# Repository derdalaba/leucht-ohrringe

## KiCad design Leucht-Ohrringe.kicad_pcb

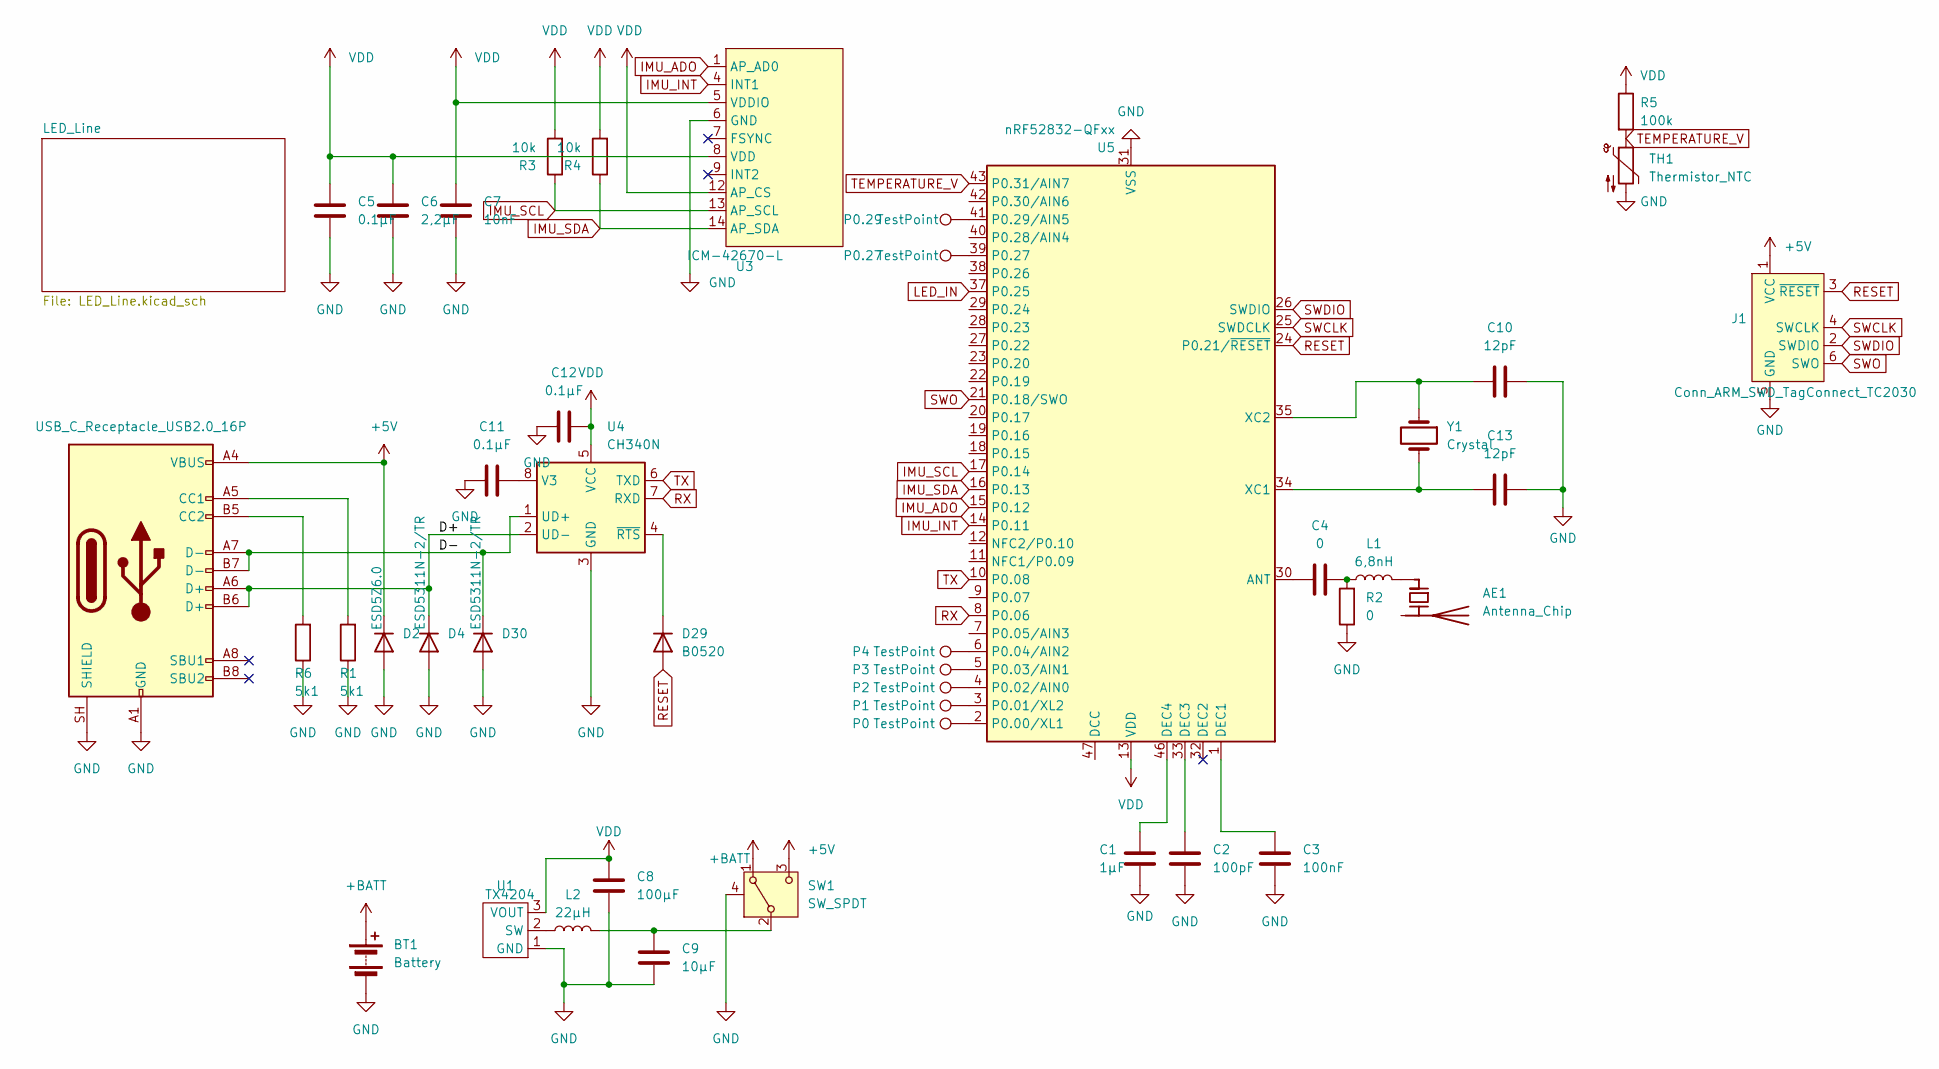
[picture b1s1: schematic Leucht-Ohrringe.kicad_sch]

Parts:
AE1: Antenna_Chip; RFANT3216120A5T; LCSC C127629
BT1: Battery; JST_SH_SM02B-SRSS-TB_1x02-1MP_P1.00mm_Horizontal
C1: 1µF; C_0402_1005Metric; LCSC C52923
C2: 100pF; C_0402_1005Metric; LCSC C1546
C3: 100nF; C_0402_1005Metric; LCSC C1525
C4: 0; C_0402_1005Metric; LCSC C17168
C5, C11, C12: 0.1µF; C_0402_1005Metric_Pad0.74x0.62mm_HandSolder; LCSC C1525
C6: 2,2µF; C_0402_1005Metric_Pad0.74x0.62mm_HandSolder; LCSC C12530
C7: 10nF; C_0402_1005Metric_Pad0.74x0.62mm_HandSolder; LCSC C15195
C8: 100µF; C_1206_3216Metric_Pad1.33x1.80mm_HandSolder; LCSC C15008
C9: 10µF; C_0603_1608Metric_Pad1.08x0.95mm_HandSolder; LCSC C19702
C10, C13: 12pF; C_0402_1005Metric; LCSC C106201
D2: ESD5Z6.0; D_SOD-523; LCSC C49437732
D4, D30: ESD5311N-2/TR; D_SOD-882; LCSC C153721
D29: B0520; D_SOD-523; LCSC C2910120
J1: Conn_ARM_SWD_TagConnect_TC2030; Tag-Connect_TC2030-IDC-NL_2x03_P1.27mm_Vertical
L1: 6,8nH; L_0402_1005Metric; LCSC C77110
L2: 22µH; FNR3015S; LCSC C167761
LCSC1: USB_C_Receptacle_USB2.0_16P; LCSC C668623
P0, P0.27, P0.29, P1, P2, P3, P4: TestPoint; TestPoint_Pad_D1.0mm
R1, R6: 5k1; R_0603_1608Metric; LCSC C2907044
R2: 0; R_0402_1005Metric; LCSC C17168
R3, R4: 10k; R_0402_1005Metric_Pad0.72x0.64mm_HandSolder; LCSC C49247682
R5: 100k; R_0402_1005Metric_Pad0.72x0.64mm_HandSolder; LCSC C25741
SW1: SW_SPDT; K3-1236S
TH1: Thermistor_NTC; R_0402_1005Metric_Pad0.72x0.64mm_HandSolder; LCSC C49247682
U1: TX4204; SOT-23-3; LCSC C5122342
U3: ICM-42670-L; Bosch_LGA-14_3x2.5mm_P0.5mm; LCSC C49073546
U4: CH340N; JEITA_SOIC-8_3.9x4.9mm_P1.27mm; LCSC C2977777
U5: nRF52832-QFxx; QFN-48-1EP_6x6mm_P0.4mm_EP4.6x4.6mm
Y1: Crystal; Crystal_SMD_2016-4Pin_2.0x1.6mm; LCSC C2682773

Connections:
+5V: D2.1 (K), J1.1 (VCC), LCSC1.A4 (VBUS), LCSC1.A9 (VBUS), LCSC1.B4 (VBUS), LCSC1.B9 (VBUS), SW1.3 (C); also elsewhere on the board
+BATT: BT1.1 (+), SW1.1 (A); also elsewhere on the board
/D+: D4.1 (K), LCSC1.A6 (D+), LCSC1.B6 (D+), U4.2 (UD-); also elsewhere on the board
/D-: D30.1 (K), LCSC1.A7 (D-), LCSC1.B7 (D-), U4.1 (UD+); also elsewhere on the board
GND: BT1.2 (-), BT1.MP, C1.2, C2.2, C3.2, C5.1, C6.2, C7.1, C8.2, C9.2, C10.2, C11.2, C12.2, C13.2, D2.2 (A), D4.2 (A), D30.2 (A), J1.5 (GND), LCSC1.A1 (GND), LCSC1.A12 (GND), LCSC1.B1 (GND), LCSC1.B12 (GND), LCSC1.SH (SHIELD), R1.1, R2.1, R6.1, SW1.4 (SHIELD), TH1.2, U1.1 (GND), U3.6 (GND), U4.3 (GND), U5.31 (VSS), U5.45 (VSS), U5.49 (VSS), Y1.3, Y1.4; also elsewhere on the board
IMU_ADO: U3.1 (AP_AD0), U5.15 (P0.12)
IMU_INT: U3.4 (INT1), U5.14 (P0.11)
IMU_SCL: R3.1, U3.13 (AP_SCL), U5.17 (P0.14)
IMU_SDA: R4.1, U3.14 (AP_SDA), U5.16 (P0.13)
LED_IN: U5.37 (P0.25); also elsewhere on the board
unnamed: AE1.1 (FEED_1), L1.2
unnamed: C4.2, L1.1, R2.2
unnamed: D29.1 (K), U4.4 (~RTS)
unnamed 37: LCSC1.A5 (CC1), R1.2; also elsewhere on the board
unnamed 38: LCSC1.B5 (CC2), R6.2; also elsewhere on the board
unnamed: C9.1, L2.2, SW1.2 (B)
unnamed: L2.1, U1.2 (SW)
unnamed: C11.1, U4.8 (V3)
unnamed: C4.1, U5.30 (ANT)
unnamed: C3.1, U5.1 (DEC1)
unnamed: C2.1, U5.33 (DEC3)
unnamed: C1.1, U5.46 (DEC4)
unnamed: P0.1 (1_1), U5.2 (P0.00/XL1)
unnamed: P1.1 (1_1), U5.3 (P0.01/XL2)
unnamed: P2.1 (1_1), U5.4 (P0.02/AIN0)
unnamed: P3.1 (1_1), U5.5 (P0.03/AIN1)
unnamed: P4.1 (1_1), U5.6 (P0.04/AIN2)
unnamed 51: P0.27.1, U5.39 (P0.27); also elsewhere on the board
unnamed 52: P0.29.1, U5.41 (P0.29/AIN5); also elsewhere on the board
unnamed: C13.1, U5.34 (XC1), Y1.2
unnamed: C10.1, U5.35 (XC2), Y1.1
RESET: D29.2 (A), J1.3 (~RESET), U5.24 (P0.21/~RESET)
RX: U4.7 (RXD), U5.8 (P0.06)
SWCLK: J1.4 (SWCLK), U5.25 (SWDCLK)
SWDIO: J1.2 (SWDIO), U5.26 (SWDIO)
SWO: J1.6 (SWO), U5.21 (P0.18/SWO)
TEMPERATURE_V: R5.2, TH1.1, U5.43 (P0.31/AIN7)
TX: U4.6 (TXD), U5.10 (P0.08)
VDD: C5.2, C6.1, C7.2, C8.1, C12.1, R3.2, R4.2, R5.1, U1.3 (VOUT), U3.5 (VDDIO), U3.8 (VDD), U3.12 (AP_CS), U4.5 (VCC), U5.13 (VDD), U5.36 (VDD), U5.48 (VDD)

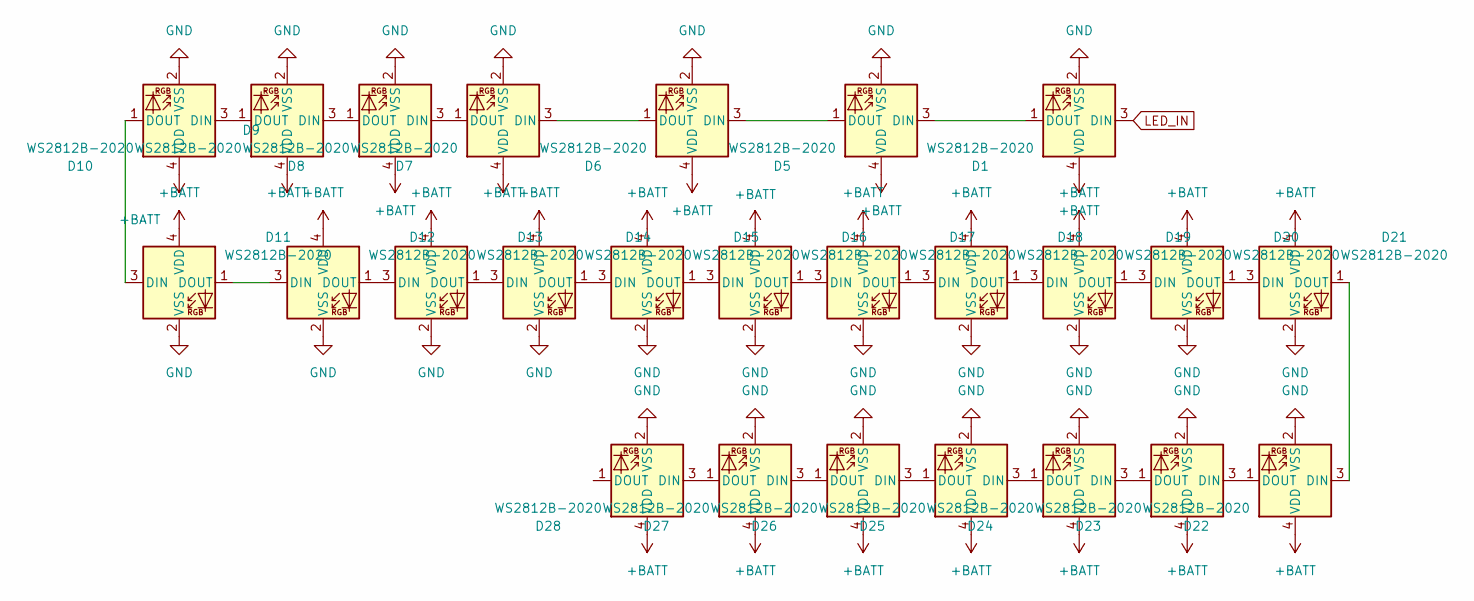
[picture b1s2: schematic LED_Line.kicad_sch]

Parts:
D1, D5, D6, D7, D8, D9, D10, D11, D12, D13, D14, D15, D16, D17, D18, D19, D20, D21, D22, D23, D24, D25, D26, D27, D28: WS2812B-2020; LED_WS2812B-2020_PLCC4_2.0x2.0mm

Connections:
+BATT: D1.4 (VDD), D5.4 (VDD), D6.4 (VDD), D7.4 (VDD), D8.4 (VDD), D9.4 (VDD), D10.4 (VDD), D11.4 (VDD), D12.4 (VDD), D13.4 (VDD), D14.4 (VDD), D15.4 (VDD), D16.4 (VDD), D17.4 (VDD), D18.4 (VDD), D19.4 (VDD), D20.4 (VDD), D21.4 (VDD), D22.4 (VDD), D23.4 (VDD), D24.4 (VDD), D25.4 (VDD), D26.4 (VDD), D27.4 (VDD), D28.4 (VDD); also elsewhere on the board
GND: D1.2 (VSS), D5.2 (VSS), D6.2 (VSS), D7.2 (VSS), D8.2 (VSS), D9.2 (VSS), D10.2 (VSS), D11.2 (VSS), D12.2 (VSS), D13.2 (VSS), D14.2 (VSS), D15.2 (VSS), D16.2 (VSS), D17.2 (VSS), D18.2 (VSS), D19.2 (VSS), D20.2 (VSS), D21.2 (VSS), D22.2 (VSS), D23.2 (VSS), D24.2 (VSS), D25.2 (VSS), D26.2 (VSS), D27.2 (VSS), D28.2 (VSS); also elsewhere on the board
LED_IN: D1.3 (DIN); also elsewhere on the board
unnamed: D1.1 (DOUT), D5.3 (DIN)
unnamed: D5.1 (DOUT), D6.3 (DIN)
unnamed: D6.1 (DOUT), D7.3 (DIN)
unnamed: D7.1 (DOUT), D8.3 (DIN)
unnamed: D8.1 (DOUT), D9.3 (DIN)
unnamed: D9.1 (DOUT), D10.3 (DIN)
unnamed: D10.1 (DOUT), D11.3 (DIN)
unnamed: D11.1 (DOUT), D12.3 (DIN)
unnamed: D12.1 (DOUT), D13.3 (DIN)
unnamed: D13.1 (DOUT), D14.3 (DIN)
unnamed: D14.1 (DOUT), D15.3 (DIN)
unnamed: D15.1 (DOUT), D16.3 (DIN)
unnamed: D16.1 (DOUT), D17.3 (DIN)
unnamed: D17.1 (DOUT), D18.3 (DIN)
unnamed: D18.1 (DOUT), D19.3 (DIN)
unnamed: D19.1 (DOUT), D20.3 (DIN)
unnamed: D20.1 (DOUT), D21.3 (DIN)
unnamed: D21.1 (DOUT), D22.3 (DIN)
unnamed: D22.1 (DOUT), D23.3 (DIN)
unnamed: D23.1 (DOUT), D24.3 (DIN)
unnamed: D24.1 (DOUT), D25.3 (DIN)
unnamed: D25.1 (DOUT), D26.3 (DIN)
unnamed: D26.1 (DOUT), D27.3 (DIN)
unnamed: D27.1 (DOUT), D28.3 (DIN)

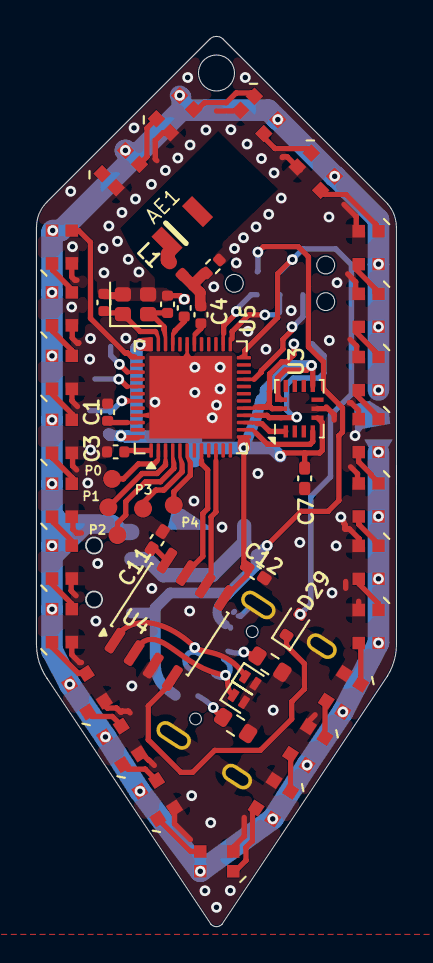
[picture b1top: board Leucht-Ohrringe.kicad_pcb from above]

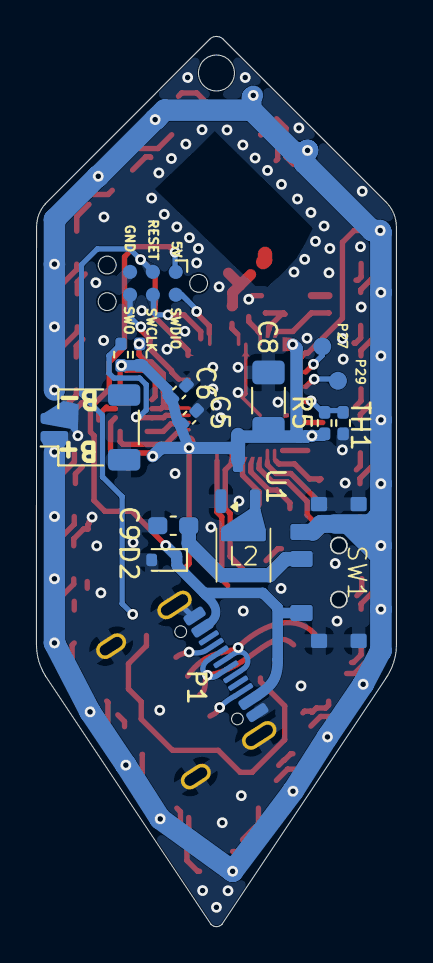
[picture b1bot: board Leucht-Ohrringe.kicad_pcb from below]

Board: 2 copper layers, 20.0 x 49.5 mm, 68 parts (17 on the bottom side), 63 nets.

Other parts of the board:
P1#2: USB_C_Plug_USB2.0; USB_C_Receptacle_G-Switch_GT-USB-7010ASV
P27, P29: TestPoint; TestPoint_Pad_D1.0mm

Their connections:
+5V: P1#2.A4 (VBUS), P1#2.A9 (VBUS), P1#2.B4 (VBUS), P1#2.B9 (VBUS); also elsewhere on the board
/D+: P1#2.A7 (D-), P1#2.B7; also elsewhere on the board
/D-: P1#2.A6 (D+), P1#2.B6; also elsewhere on the board
GND: P1#2.A1 (GND), P1#2.A12 (GND), P1#2.B1 (GND), P1#2.B12 (GND), P1#2.SH (SHIELD); also elsewhere on the board
unnamed 37: P1#2.A5 (CC); also elsewhere on the board
unnamed 38: P1#2.B5 (VCONN); also elsewhere on the board
unnamed 51: P27.1 (1_1); also elsewhere on the board
unnamed 52: P29.1 (1_1); also elsewhere on the board

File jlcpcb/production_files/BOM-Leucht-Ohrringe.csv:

Comment,Designator,Footprint,LCSC,Quantity
0,"C4,R2",C_0402_1005Metric,C17168,2
0.1µF,"C11,C12,C5",C_0402_1005Metric_Pad0.74x0.62mm_HandSolder,C1525,3
100k,R5,R_0402_1005Metric_Pad0.72x0.64mm_HandSolder,C25741,1
100nF,C3,C_0402_1005Metric,C1525,1
100pF,C2,C_0402_1005Metric,C1546,1
100µF,C8,C_1206_3216Metric_Pad1.33x1.80mm_HandSolder,C15008,1
10k,"R3,R4",R_0402_1005Metric_Pad0.72x0.64mm_HandSolder,C25744,2
10nF,C7,C_0402_1005Metric_Pad0.74x0.62mm_HandSolder,C15195,1
10µF,C9,C_0603_1608Metric_Pad1.08x0.95mm_HandSolder,C19702,1
1µF,C1,C_0402_1005Metric,C52923,1
"2,2µF",C6,C_0402_1005Metric_Pad0.74x0.62mm_HandSolder,C12530,1
22µH,L2,FNR3015S,C167761,1
5k1,R1,R_0603_1608Metric,C23186,1
"6,8nH",L1,L_0402_1005Metric,C77110,1
Antenna_Chip,AE1,RFANT3216120A5T,C127629,1
B0520,D29,D_SOD-523,C2910120,1
CH340N,U4,JEITA_SOIC-8_3.9x4.9mm_P1.27mm,C2977777,1
ESD5Z6.0,D2,D_SOD-523,C49437732,1
H4V5HD3UA,"D3,D4",D_SOD-323,C54334010,2
ICM-42670-L,U3,Bosch_LGA-14_3x2.5mm_P0.5mm,C49073546,1
TX4204,U1,SOT-23-3,C5122342,1
Thermistor_NTC,TH1,R_0402_1005Metric_Pad0.72x0.64mm_HandSolder,C49247682,1
USB_C_Plug_USB2.0,P1,USB_C_Receptacle_G-Switch_GT-USB-7010ASV,C668623,1
nRF52832-QFxx,U5,QFN-48-1EP_6x6mm_P0.4mm_EP4.6x4.6mm,C77540,1
WS2812B-2020,D23,LED_WS2812B-2020_PLCC4_2.0x2.0mm,,1
WS2812B-2020,D26,LED_WS2812B-2020_PLCC4_2.0x2.0mm,,1
WS2812B-2020,D20,LED_WS2812B-2020_PLCC4_2.0x2.0mm,,1
WS2812B-2020,D21,LED_WS2812B-2020_PLCC4_2.0x2.0mm,,1
WS2812B-2020,D18,LED_WS2812B-2020_PLCC4_2.0x2.0mm,,1
WS2812B-2020,D14,LED_WS2812B-2020_PLCC4_2.0x2.0mm,,1
WS2812B-2020,D25,LED_WS2812B-2020_PLCC4_2.0x2.0mm,,1
WS2812B-2020,D22,LED_WS2812B-2020_PLCC4_2.0x2.0mm,,1
WS2812B-2020,D19,LED_WS2812B-2020_PLCC4_2.0x2.0mm,,1
WS2812B-2020,D5,LED_WS2812B-2020_PLCC4_2.0x2.0mm,,1
WS2812B-2020,D11,LED_WS2812B-2020_PLCC4_2.0x2.0mm,,1
WS2812B-2020,D13,LED_WS2812B-2020_PLCC4_2.0x2.0mm,,1
WS2812B-2020,D24,LED_WS2812B-2020_PLCC4_2.0x2.0mm,,1
WS2812B-2020,D8,LED_WS2812B-2020_PLCC4_2.0x2.0mm,,1
WS2812B-2020,D10,LED_WS2812B-2020_PLCC4_2.0x2.0mm,,1
WS2812B-2020,D1,LED_WS2812B-2020_PLCC4_2.0x2.0mm,,1
WS2812B-2020,D6,LED_WS2812B-2020_PLCC4_2.0x2.0mm,,1
WS2812B-2020,D7,LED_WS2812B-2020_PLCC4_2.0x2.0mm,,1
WS2812B-2020,D16,LED_WS2812B-2020_PLCC4_2.0x2.0mm,,1
WS2812B-2020,D15,LED_WS2812B-2020_PLCC4_2.0x2.0mm,,1
WS2812B-2020,D17,LED_WS2812B-2020_PLCC4_2.0x2.0mm,,1
WS2812B-2020,D28,LED_WS2812B-2020_PLCC4_2.0x2.0mm,,1
WS2812B-2020,D27,LED_WS2812B-2020_PLCC4_2.0x2.0mm,,1
WS2812B-2020,D12,LED_WS2812B-2020_PLCC4_2.0x2.0mm,,1
WS2812B-2020,D9,LED_WS2812B-2020_PLCC4_2.0x2.0mm,,1
Battery,BT1,JST_SH_SM02B-SRSS-TB_1x02-1MP_P1.00mm_Horizontal,,1
TestPoint,TP2,"TestPoint_0,5mm",,1
TestPoint,TP3,"TestPoint_0,5mm",,1
TestPoint,TP4,"TestPoint_0,5mm",,1
TestPoint,TP1,"TestPoint_0,5mm",,1
SW_SPDT,SW1,K3-1236S,,1
TestPoint,TP6,"TestPoint_0,5mm",,1
TestPoint,TP5,"TestPoint_0,5mm",,1
